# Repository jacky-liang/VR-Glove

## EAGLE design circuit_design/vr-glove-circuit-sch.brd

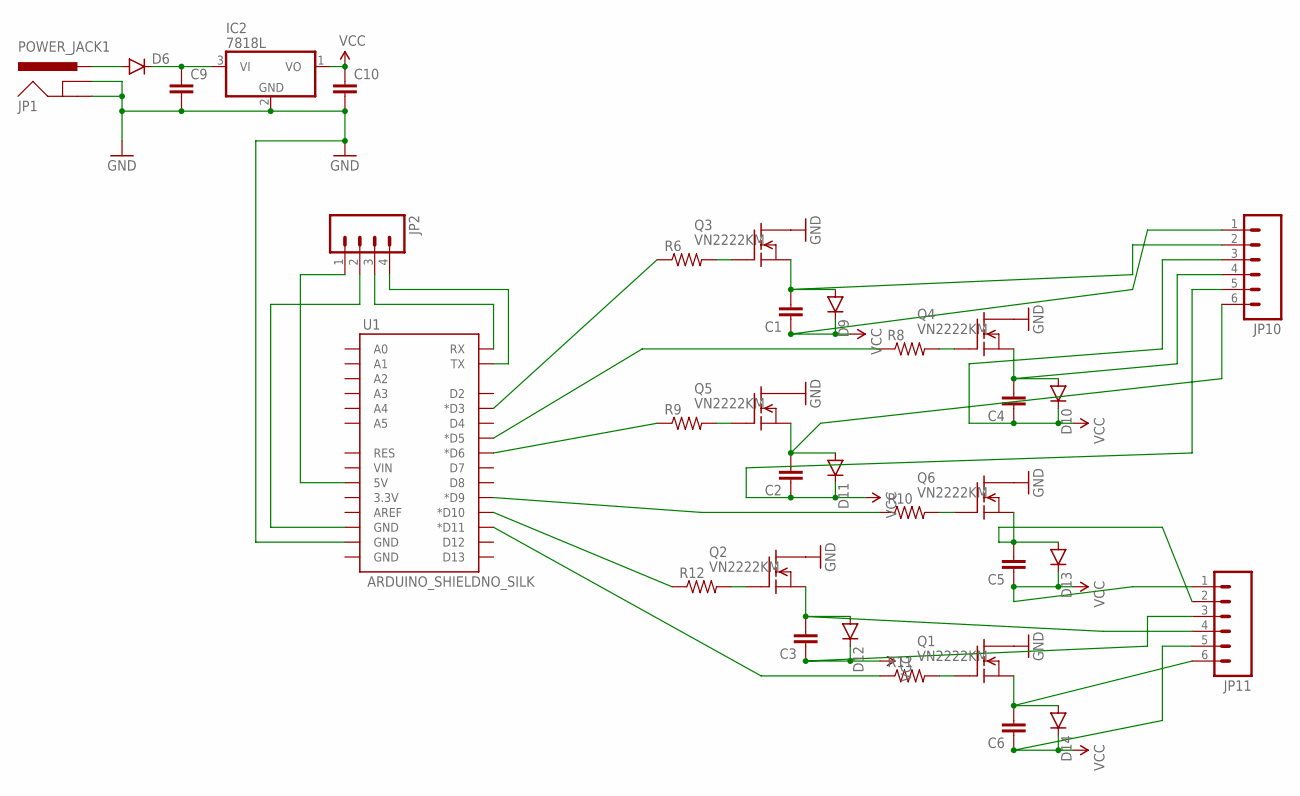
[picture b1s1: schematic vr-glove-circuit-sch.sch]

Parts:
C1, C2, C3, C4, C5, C6, C9, C10: CAPPTH; CAP-PTH-SMALL
D6, D9, D10, D11, D12, D13, D14: DIODE1N4148; DIODE-1N4148
IC2: 7818L; TO92
JP1: POWER_JACK1; POWER_JACK_SMD_OVERPASTE_REDBOARD_0603
JP2: M04LOCK; 1X04_LOCK
JP10, JP11: M06SILK_FEMALE_PTH; 1X06
Q1, Q2, Q3, Q4, Q5, Q6: VN2222KM; TO237
R6, R8, R9, R10, R11, R12: RESISTORPTH-1/4W-VERT; AXIAL-0.1
U1: ARDUINO_SHIELDNO_SILK; DUEMILANOVE_VIAS

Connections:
GND: C9.2, C10.2, IC2.2 (GND), JP1.GND (GNDBREAK), JP1.P$4 (GND), Q1.1 (D), Q2.1 (D), Q3.1 (D), Q4.1 (D), Q5.1 (D), Q6.1 (D), U1.GND@1 (GND)
unnamed: Q3.2 (G), R6.P$2 (2)
unnamed: C1.2, D9.A, JP10.2, Q3.3 (S)
unnamed: JP2.2, U1.GND@2 (GND)
unnamed: Q5.2 (G), R9.P$2 (2)
unnamed: C2.2, D11.A, JP10.6, Q5.3 (S)
unnamed: JP2.1, U1.5V
unnamed: Q2.2 (G), R12.P$2 (2)
unnamed: C3.2, D12.A, JP11.4, Q2.3 (S)
unnamed: D6.A, JP1.VIN0 (PWR)
unnamed: Q4.2 (G), R8.P$2 (2)
unnamed: C4.2, D10.A, JP10.4, Q4.3 (S)
unnamed: JP2.3, U1.RX
unnamed: Q6.2 (G), R10.P$2 (2)
unnamed: C5.2, D13.A, JP11.2, Q6.3 (S)
unnamed: JP2.4, U1.TX
unnamed: Q1.2 (G), R11.P$2 (2)
unnamed: C6.2, D14.A, JP11.6, Q1.3 (S)
unnamed: C9.1, D6.C, IC2.3 (VI)
unnamed: R6.P$1 (1), U1.D3 (*D3)
unnamed: R8.P$1 (1), U1.D5 (*D5)
unnamed: R9.P$1 (1), U1.D6 (*D6)
unnamed: R10.P$1 (1), U1.D9 (*D9)
unnamed: R12.P$1 (1), U1.D10 (*D10)
unnamed: R11.P$1 (1), U1.D11 (*D11)
VCC: C1.1, C2.1, C3.1, C4.1, C5.1, C6.1, C10.1, D9.C, D10.C, D11.C, D12.C, D13.C, D14.C, IC2.1 (VO), JP10.1, JP10.3, JP10.5, JP11.1, JP11.3, JP11.5

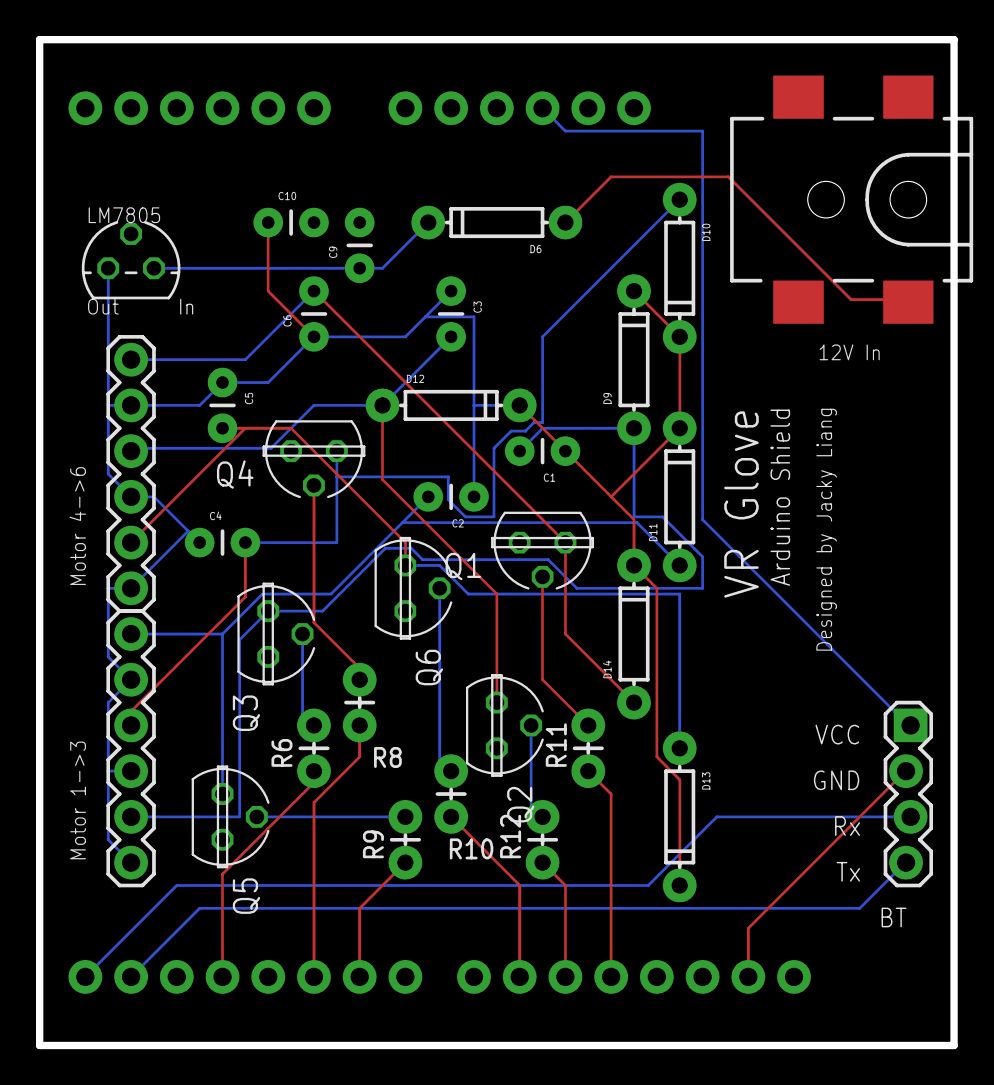
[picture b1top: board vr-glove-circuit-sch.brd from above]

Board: 2 copper layers, 50.8 x 55.9 mm, 33 parts (0 on the bottom side), 26 nets.

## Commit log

2015-02-06 init commit
2015-02-13 Setup for Lab Computer. Fixed Leap DLL issue. Adjusted Camera Position
2015-02-19 finished simple node server and communication interface between unity and node.
2015-02-19 finished linking unity vibration sending with networking module.
2015-02-26 completed server bt code. arduino still can't receive msg
2015-02-27 bluetooth working
2015-02-27 added circuit file
2015-02-27 modified communication protocol to work with web safe characters
2015-03-06 started circuit design with eagle
2015-03-06 saved
2015-03-09 added power supply
2015-03-09 finished initial design for schematic and board. still need to complete silkscreen labels and testing.
2015-03-11 finialized circuit design
2015-03-19 working wireless communication
2015-03-19 improved bt server
2015-03-19 removed delay time for arduino loop
2015-03-19 used coroutine for sending requests

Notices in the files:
parts and their libraries:
SparkFun-Capacitors: Licensing: Creative Commons ShareAlike 4.0 International - https://creativecommons.org/licenses/by-sa/4.0
